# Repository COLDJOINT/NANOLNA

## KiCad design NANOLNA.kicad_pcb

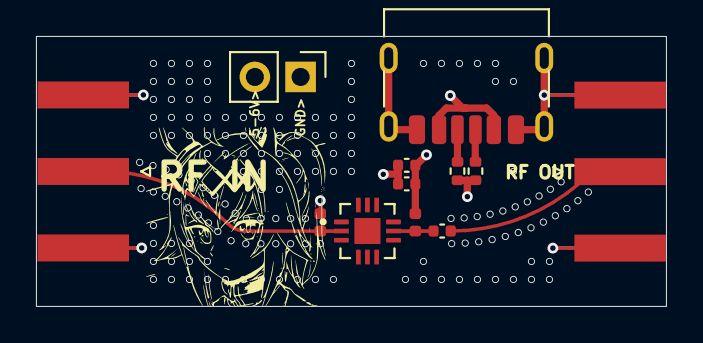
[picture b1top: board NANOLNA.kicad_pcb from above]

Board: 4 copper layers, 35.0 x 15.0 mm, 12 parts (0 on the bottom side), 7 nets.

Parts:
C1: 10nF; C_0402_1005Metric
C2: 10pF; C_0402_1005Metric
C3: 100pF; C_0402_1005Metric
J1, J3: Conn_Coaxial; SMA_Amphenol_132289_EdgeMount
J2: USB_C_Receptacle_PowerOnly_6P; USB_C_Receptacle_HRO_TYPE-C-31-M-17
J4: JST MOUNT; PinHeader_1x02_P2.54mm_Vertical
L1: 18nH; L_0402_1005Metric
L2: 39nH; L_0402_1005Metric
R1, R2: 5.1K; R_0402_1005Metric
U1: PMA3-83LN_; QFN51P300X300X89-13N

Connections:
/WIDEBAND LNA/RF IN: J1.1 (In), L1.1, U1.2
/WIDEBAND LNA/RF OUT: C3.1, L2.2, U1.8
GND: C1.2, C2.2, J1.2 (Ext), J2.A12 (GND), J2.B12 (GND), J2.S1 (SHIELD), J3.2 (Ext), J4.1, L1.2, R1.2, R2.1, U1.13
unnamed: J2.A5 (CC1), R1.1
unnamed: J2.B5 (CC2), R2.2
unnamed: C3.2, J3.1 (In)
VBUS: C1.1, C2.1, J2.A9 (VBUS), J2.B9 (VBUS), J4.2, L2.1
